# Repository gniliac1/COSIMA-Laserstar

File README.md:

COSIMA-Laserstar
================

Hier entsteht das Repository für den COSIMA-Wettbewerb.

Weitere Infos folgen in Kürze ...

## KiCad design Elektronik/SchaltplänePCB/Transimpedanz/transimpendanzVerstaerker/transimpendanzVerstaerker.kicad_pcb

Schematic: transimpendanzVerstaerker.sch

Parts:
C1: 1pF; C_0805_2012Metric_Pad1.15x1.40mm_HandSolder
D1: IR204A; LED_D3.0mm_IRBlack
J1: con1; FanPinHeader_1x03_P2.54mm_Vertical
R1: 1MOhm; R_0805_2012Metric_Pad1.15x1.40mm_HandSolder
U1: LM358; SOIC-8_3.9x4.9mm_P1.27mm

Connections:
unnamed: C1.1, J1.2, R1.1, U1.1
unnamed: C1.2, D1.1 (K), R1.2, U1.2 (-)
unnamed: D1.2 (A), J1.1, U1.3 (+), U1.4 (V-)
unnamed: J1.3, U1.8 (V+)

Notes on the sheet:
5V Out GND

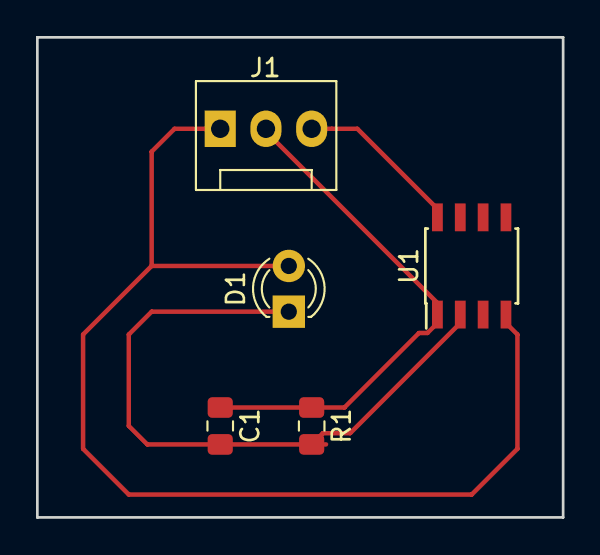
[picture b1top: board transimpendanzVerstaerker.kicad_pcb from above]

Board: 2 copper layers, 29.2 x 26.7 mm, 5 parts (0 on the bottom side), 4 nets.

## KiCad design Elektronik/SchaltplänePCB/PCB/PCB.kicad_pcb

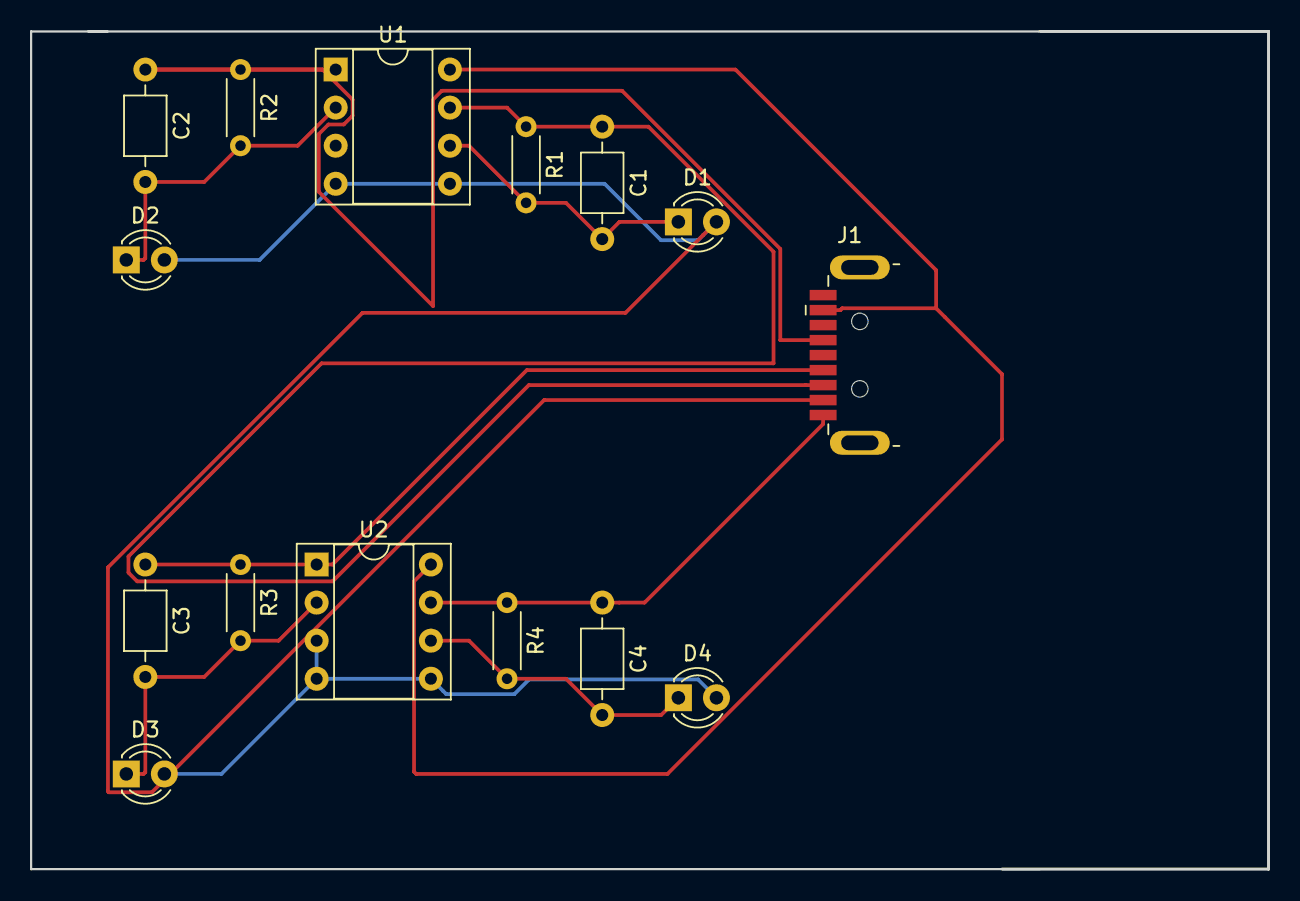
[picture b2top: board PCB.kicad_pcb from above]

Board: 2 copper layers, 82.5 x 55.9 mm, 15 parts (0 on the bottom side), 10 nets.

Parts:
C1, C2, C3, C4: C; C_Axial_L3.8mm_D2.6mm_P7.50mm_Horizontal
D1, D2, D3, D4: LED; LED_D3.0mm_Clear
J1: USB3_A; USB3_A_Plug_Wuerth_692112030100_Horizontal
R1, R2, R3, R4: R; R_Axial_DIN0204_L3.6mm_D1.6mm_P5.08mm_Horizontal
U1, U2: LM358; DIP-8_W7.62mm_Socket

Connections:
GND: D1.2, D2.2, D3.2, D4.2, J1.4, U1.3, U1.4, U1.5, U2.3, U2.4, U2.5
unnamed: C1.1, J1.6, R1.1, U1.7
unnamed: C1.2, D1.1, R1.2, U1.6
unnamed: C2.1, J1.2, R2.1, U1.1
unnamed: C2.2, D2.1, R2.2, U1.2
unnamed: C3.1, J1.3, R3.1, U2.1
unnamed: C3.2, D3.1, R3.2, U2.2
unnamed: C4.1, J1.5, R4.1, U2.7
unnamed: C4.2, D4.1, R4.2, U2.6
unnamed: J1.1, U1.8, U2.8

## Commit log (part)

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2018-05-16 Repository eröffnet!
2018-05-16 PPT-Treffen 2018-05-17
2018-05-16 PPT Komprimiert
2018-05-16 maschine learning teil hinzugefügt
2018-05-17 PPT 17.05.2018 TODOS
2018-05-18 Einzelfotos vom Team
2018-05-27 Kurzbeschreibung Cailing
2018-06-01 Kurzbeschreibung Daniel
2018-06-21 word dokument umbenannt
2018-06-21 Präsentation überarbeitet
    Ich habe hier und da mal ein paar Kommentare unter den Folien gemacht. Schaut euch die Präsentation noch mal an und sagt mir, was ihr davon haltet :)
2018-07-02 Ideen für MachineLearning
2018-07-06 Teambeschreibung überarbeitet
2018-07-11 Präsentation verbessert
2018-07-12 update Präsentation
2018-07-14 Added Datasheets
    2 mögliche Photodioden
    I^2C bus-Adressen
2018-07-16 Added Datasheet
    Added datasheet PCA8574 i^2c I/O Expander
2018-07-17 Added Schematic
    Schaltplan für den I2C-Expander (nur zwei IR-LEDS eingefügt)
2018-07-19 Bilder für die Präsi
2018-07-19 EIn Bild vergessen
2018-07-19 Präsentation überarbeitet
    - Habe unser Konzept mit der Photoplatte hinzugefügt.
    Verbesserungsvorschläge erwünscht
    - Der Text für "Unser Produkt" und "Anwendungsmöglichkeiten" wurde noch
    nicht überarbeitet
2018-07-26 präsentation bearbeitet
2018-07-26 Addon
    Added Instagram folder and uploaded circuit pictures
2018-07-26 Test_grubert
    Das ist eine Datei um das commiten zu lernen
2018-07-26 Test2
    TEstetest
2018-07-26 Revert "Test2"
    This reverts commit 87898f6974b88c0d0bbb372ebc9380703e303fe4.
2018-07-26 pptx datei
2018-07-26 Folien als pdf, Sponsorentabelle
2018-07-26 noch irgendwas geändert
2018-07-26 vectors
2018-07-30 Teamvorstellung
    Kurzbeschreibung Nicole
2018-08-01 sponsorenliste überarbeitet
2018-08-03 Anwendungsmöglichkeiten und Produktbeschreibung geändert
2018-08-05 machine learning how to install and to use
2018-08-05 Dokumentiertes Beispiel für Benutzung von TensorFlow hinzugefügt
    Aufruf aus der Konsole / Terminal mittels:
    python tf_tutorial.py
2018-08-05 Reading data from .csv file
2018-08-05 Überlegungen zum Ablauf des Machine Learnings
2018-08-05 Added new files
    -arduino code for rc car (unfinished slightly working)
    -hugo pictuer for instagram
2018-08-05 export database with 10% test and 90% train data
2018-08-05 erster Entwurf für eigenes Modell mit zwei Ausgabeparamtern
    noch nicht fertig!!!
2018-08-06 Sponsorenwerben
2018-08-06 Sponsoren
    Email an:
    RS Components
    Reichelt
    fanuc
2018-08-06 marketing updated
2018-08-06 update Sponsorenliste
    Neue potentielle Sponsoren hinzugefügt
2018-08-06 Neue Fotos
2018-08-06 Added Datasheet for strain gauges
2018-08-06 Biegesensor
    Der aus dem Powerglove!!! den will ich haben!!!
2018-08-06 Added template for serial communication
2018-08-06 keras model functions for saving and such stuff
2018-08-06 erstes neuronales Modell zur vorhersage kontinuierlicher Daten
2018-08-07 created folder CAD
    Added cad file for octagon
    Added pictures and measurements for the rc car
2018-08-07 Sponsoren Präsentation vervollständigt
    - Nicole hinzugefügt
    - Die beschreibungen von Daniel hinzugefügt
2018-08-07 Bluetooth connecivity and rearrangement
2018-08-08 bidirectional bluetooth communication
    Not yet tested. How to prevent fuckups like trying to read, while sending data?
2018-08-08 Test
    Test
2018-08-08 Löschen
    Test
2018-08-08 Update Sponsorenliste
    neue Sponsoren
    neue Emailadressen
2018-08-08 Elektrofachhändler als Sponsoren
    Media Markt & Saturn Aachen
2018-08-08 Bilder für Website
2018-08-08 Update
    Sponsoren angerufen
2018-08-08 projektbeschreibung angefangen
    noch nicht fertig, wird weiter fortgesetzt
2018-08-09 Projektbeschreibung fortgeführt
    es fehlt der Abschnitt zum Machine Learning
2018-08-09 Sixt als Sponsor ?
2018-08-09 update sponsorliste
2018-08-09 Export .ipt to .step
2018-08-09 Projektbeschreibung weitergemacht
2018-08-10 Projektbeschreibeiter gemacht
    Fehlt nur noch ein ausformulierter Abschnitt zu den Anwendungsmöglichkeiten
2018-08-10 test
    tets
2018-08-10 update für gitignore
2018-08-10 update for bluetoothcommunication
2018-08-10 BluetoothExperiments
2018-08-11 projektbeschreibung fertig
2018-08-12 Read Sensor/ write to bluetooth
2018-08-12 Added pic for instagram
2018-08-12 Abbildungen für die Software erstellt
    + Ordner "Machine Learning" in "Software" umbenannt
    + Projektbeschreibung etwas überarbeitet
    + Flussdiagramm, Ablaufdiagramme und Use Case vollständig
    TODO:
    + Klassendiagramm muss noch erstellt werden
2018-08-13 Implemented i2c, ADS1015
    Implemented:
    -i2c wiring
    -Ardafriut library for easy communication with the ads1015 protboard (Needs testing!)
    -Bluetooth communication to python still available
2018-08-13 Added exit for bluetooth conection
    Needs testing
2018-08-13 deleted unused serialCommunication.ino
2018-08-13 deleted unused serialComPython.py
2018-08-13 removed mistake(s)
2018-08-13 Ein Stück Klassendiagramm
2018-08-13 test
2018-08-15 update sponsoring
    Absagen u. neue Sponsoren
2018-08-15 Update Elektronik
    -Deleted unused files
    -Added PCB Files for OPAmp
    -Updated Python script for
    serial communication
2018-08-15 Mehr Diagramme und Code angefangen
2018-08-16 Bluetooth Remotecontrol for RC car
2018-08-16 removed errors
2018-08-16 added bluetooth "remote" for rc car
2018-08-16 added sleep for keyboard detection
2018-08-16 updated and finished pcb designe for opamo
2018-08-16 finished test pcb layout
2018-08-16 removed titles
2018-08-16 Etwas Rahmencode
2018-08-18 Notlösungs Board (WIP)
2018-08-18 Mehr Rahmen für main
2018-08-18 small bugfix
2018-08-20 Schaltplan fertig
2018-08-22 finished bluetooth communication
    tested
    works
    fun
2018-08-23 Added ESP32 PWM not working yet
2018-08-24 RC Car Working!!!
2018-08-24 Neuronales Netz mit zwei Ausgabeparamtern
2018-08-25 i2c Sensor
    -Rough tested
2018-08-25 rearragend folders
    deleted obsolete code for sensor reading
2018-08-27 tweaked oktoauto controls
2018-08-28 tweak
2018-08-31 Code for sensorGlove
2018-09-03 Read all sensorvalues
2018-09-03 finished gloves alpha
2018-09-03 Alpha.2
2018-09-03 Solved first TODO
    TODO: Testen ob öffnen und schießen besser ist
    Siehe meine Kommentare ;)
2018-09-06 updated sensorGlove
2018-09-06 coder working
2018-09-12 kleine Änderungen
2018-09-13 Skript zur Aufzeichnung von Daten angefangen
2018-09-14 improved accuracy of NN
2018-09-17 communication between arduino and python
2018-09-17 moved file
2018-09-17 first version works
2018-09-19 Kostenanpassung
    Fehler in der Summe der Kosten
2018-09-19 Kostenanpassung
    PDF
2018-09-19 kleinere Änderungen
2018-09-20 added gain for better detection of photo current changes
2018-09-20 renamed directory according to convention of arduino ide
2018-09-20 added specification sheet for i2c multiplexer
2018-09-20 added gain
2018-09-20 extended code to all multiplexers, added gain and a threshold which has to be exceeded before communicating changes
2018-09-20 renamed file
2018-09-20 added code to write data to an external file
    TODO:
    - insert linebreaks after input values and after target values
    - do some exception handlings
2018-09-21 improved reflection detection code
2018-09-21 added code for reading recorded reflection data and training a neuronal net
2018-09-21 added data for training the neuronal net
2018-09-23 changed the partition of the data to obtain less random accuracies
2018-09-24 adapted script for recording data using the glove
2018-09-24 CAD Lampignon
    stl und ipt
2018-09-24 adapted ml
2018-09-24 code for usb plug connection
2018-09-25 added data folder and moved data files
2018-09-25 adapted scripts to new folder structure
2018-09-25 changes from today including a first version of a working NN
2018-09-25 added addtional data
2018-09-26 added data sheets and code for new multiplexers as well as a todo for the time of Cailing's holidays
2018-09-26 ordered todo list by importance
2018-09-27 added datasheets for leds
2018-09-30 Ordner für Dokumentation hinzugefügt
2018-09-30 Ideen zur Konstruktion der Module hinzugefügt
2018-10-01 Oktagon
    Arduino Gehäuse
2018-10-15 Größerer Oktagon
    Änderung
2018-10-15 CAD Änderungen
2018-10-20 Platine
    Platine
2018-10-26 Abschlussbericht angefangen (in Latex)
2018-10-26 Titelblatt vorl. fertig
2018-10-26 Kapitel eingebunden und erste Überlegungen zur Gliederung
2018-10-26 main-Datei ausgemistet
2018-10-26 kleine Änderungen an der Titelseite
2018-10-26 Änderungen von Cailing an der main Datei wiederhergestellt
2018-10-26 Einleitung angefangen
2018-10-26 Ausblick angefangen
2018-10-26 Bilder aus ppt exportiert
2018-10-26 Aufbau Photoplatte vorl. Text
2018-10-26 Sponsoren hinzugefügt
2018-10-26 some layout changes
2018-10-26 layout changes
2018-10-26 continued stuff
2018-10-26 added todo
2018-10-26 Kosten vorl. fertig
2018-10-27 Report Kostenteil erwitert
2018-10-27 Logos hochgeladen
2018-10-27 changed layout of title page
2018-10-27 Poster angefangen
2018-10-27 Ordner verschoben
2018-10-27 Logo Pfade verändert
2018-10-27 Poster vorl. Version
    TODO:
    - Software Teil
    - Alle Bilder auswechseln
2018-10-27 Einleitung vorl. fertig
2018-10-27 Flyper angefangen
2018-10-27 continued software part of report
2018-10-27 added new draft for flyer
2018-10-28 Abschnitt Transimpedanz verstärker hinzugefügt
2018-10-28 kack MSWord
2018-10-28 Fritzing Scheme
    finde ich recht unübersichtlich.... kriege es aber mangels platz nicht wirklich besser hin :(...
2018-10-28 check
2018-10-28 added corrections and part of christoph to latex report
2018-10-28 transimpedanzSchem
2018-10-28 included figure of transimpedanz
2018-10-28 Schriftart geändert
2018-10-28 update Bericht compiler fail
2018-10-28 new try
2018-10-28 adapted images to cailing's changes
2018-10-28 neue bilder
2018-10-30 CAD
    Konstruktion
2018-10-30 E-Parts
    CAD-Dateien eingefügt
2018-10-31 CAD
    Oktokommander
2018-10-31 added new layout and cleaned up code
2018-11-01 .svg für Anna
2018-11-01 update für den Bericht
2018-11-01 CAD Bilder
2018-11-01 Oktokommander und Detektormodul
    CAD
2018-11-01 added chapter "Stand der Technik"
2018-11-02 Projektbericht Konstruktion
    Beschreibung der wichtigsten Besonderheiten der Konstruktion, den Aufbau und das Hinzufügen von weiteren Bildern
2018-11-02 abschnitt von nicole in den bericht aufgenommen
2018-11-03 Neue Logos und ein Video
    ILT und aconity Logo in besserer Qualität
    Video vom Zusammenbau des Gestikulasers
2018-11-03 bilder von anna
2018-11-03 bilder umbenannt und in report aufgenommen
2018-11-03 Oktopus
2018-11-03 added / renamed images
2018-11-03 reviewed content of chapter 3
2018-11-03 ich habe fertig
2018-11-03 updated title page
2018-11-04 Layout Anpassungen
2018-11-06 Logos und T-Shirts
2018-11-06 Korrekturen vom Abschlussbericht
2018-11-07 Neues TOS Logo
2018-11-07 Kosten vervollständigt
2018-11-07 Datenblätter aufgeräumt
2018-11-07 changes to 4th chapter
2018-11-07 Bilder überarbeitet
2018-11-07 reviewed chapter 4
2018-11-08 changes from marcel
2018-11-08 neue CAD Dateien und steps und ....
2018-11-08 Präsentation weiter gemacht
2018-11-08 finaler entwurf
2018-11-09 Bilder für Flyer
2018-11-09 Mehr Präsi
2018-11-09 Flyer
2018-11-09 Platinen Test Code
2018-11-10 flyer (quasi) fertig
2018-11-10 Neue CAD Bilder
2018-11-10 nicoles namen in die zweite zeile verschoben
2018-11-10 CAD und Bildmaterial geändert
    Neue Wandstärke Detektormodul, Bohrung Oktokommander angepasst.
    Bilder: Sensorhandschuh, Detektormodul und Oktokommander (Wasserfarben und raytraced aus zwei Positionen)
2018-11-10 stl Druckdateien
    7x Stage 2
    1x Stage 3
    1x Stage 2 Oktokommander
2018-11-10 poster
2018-11-11 Neue PhotoplatteBeta Bild
2018-11-11 Dateien druckoptimiert
2018-11-11 Anpassung Konstruktion
    Detektorgehäuse und Deckel angepasst
2018-11-11 update poster + flyer
2018-11-11 Balkenhöhe geändert
2018-11-12 Bilder Arduino, Anpassung Druck
2018-11-12 Bilder bearbeitet und neue hinzugefügt
2018-11-12 poster und Flyer überarbeitet
2018-11-12 Transparenter Sensorhandschuh
2018-11-12 Pfleck auf Handschuh entfernt ^^"
2018-11-12 Kleine Änderung
2018-11-13 Oktokommander Code
2018-11-13 Test für die Stecker
    Das Andere unter "Oktokommander" habe ich nicht verstanden
